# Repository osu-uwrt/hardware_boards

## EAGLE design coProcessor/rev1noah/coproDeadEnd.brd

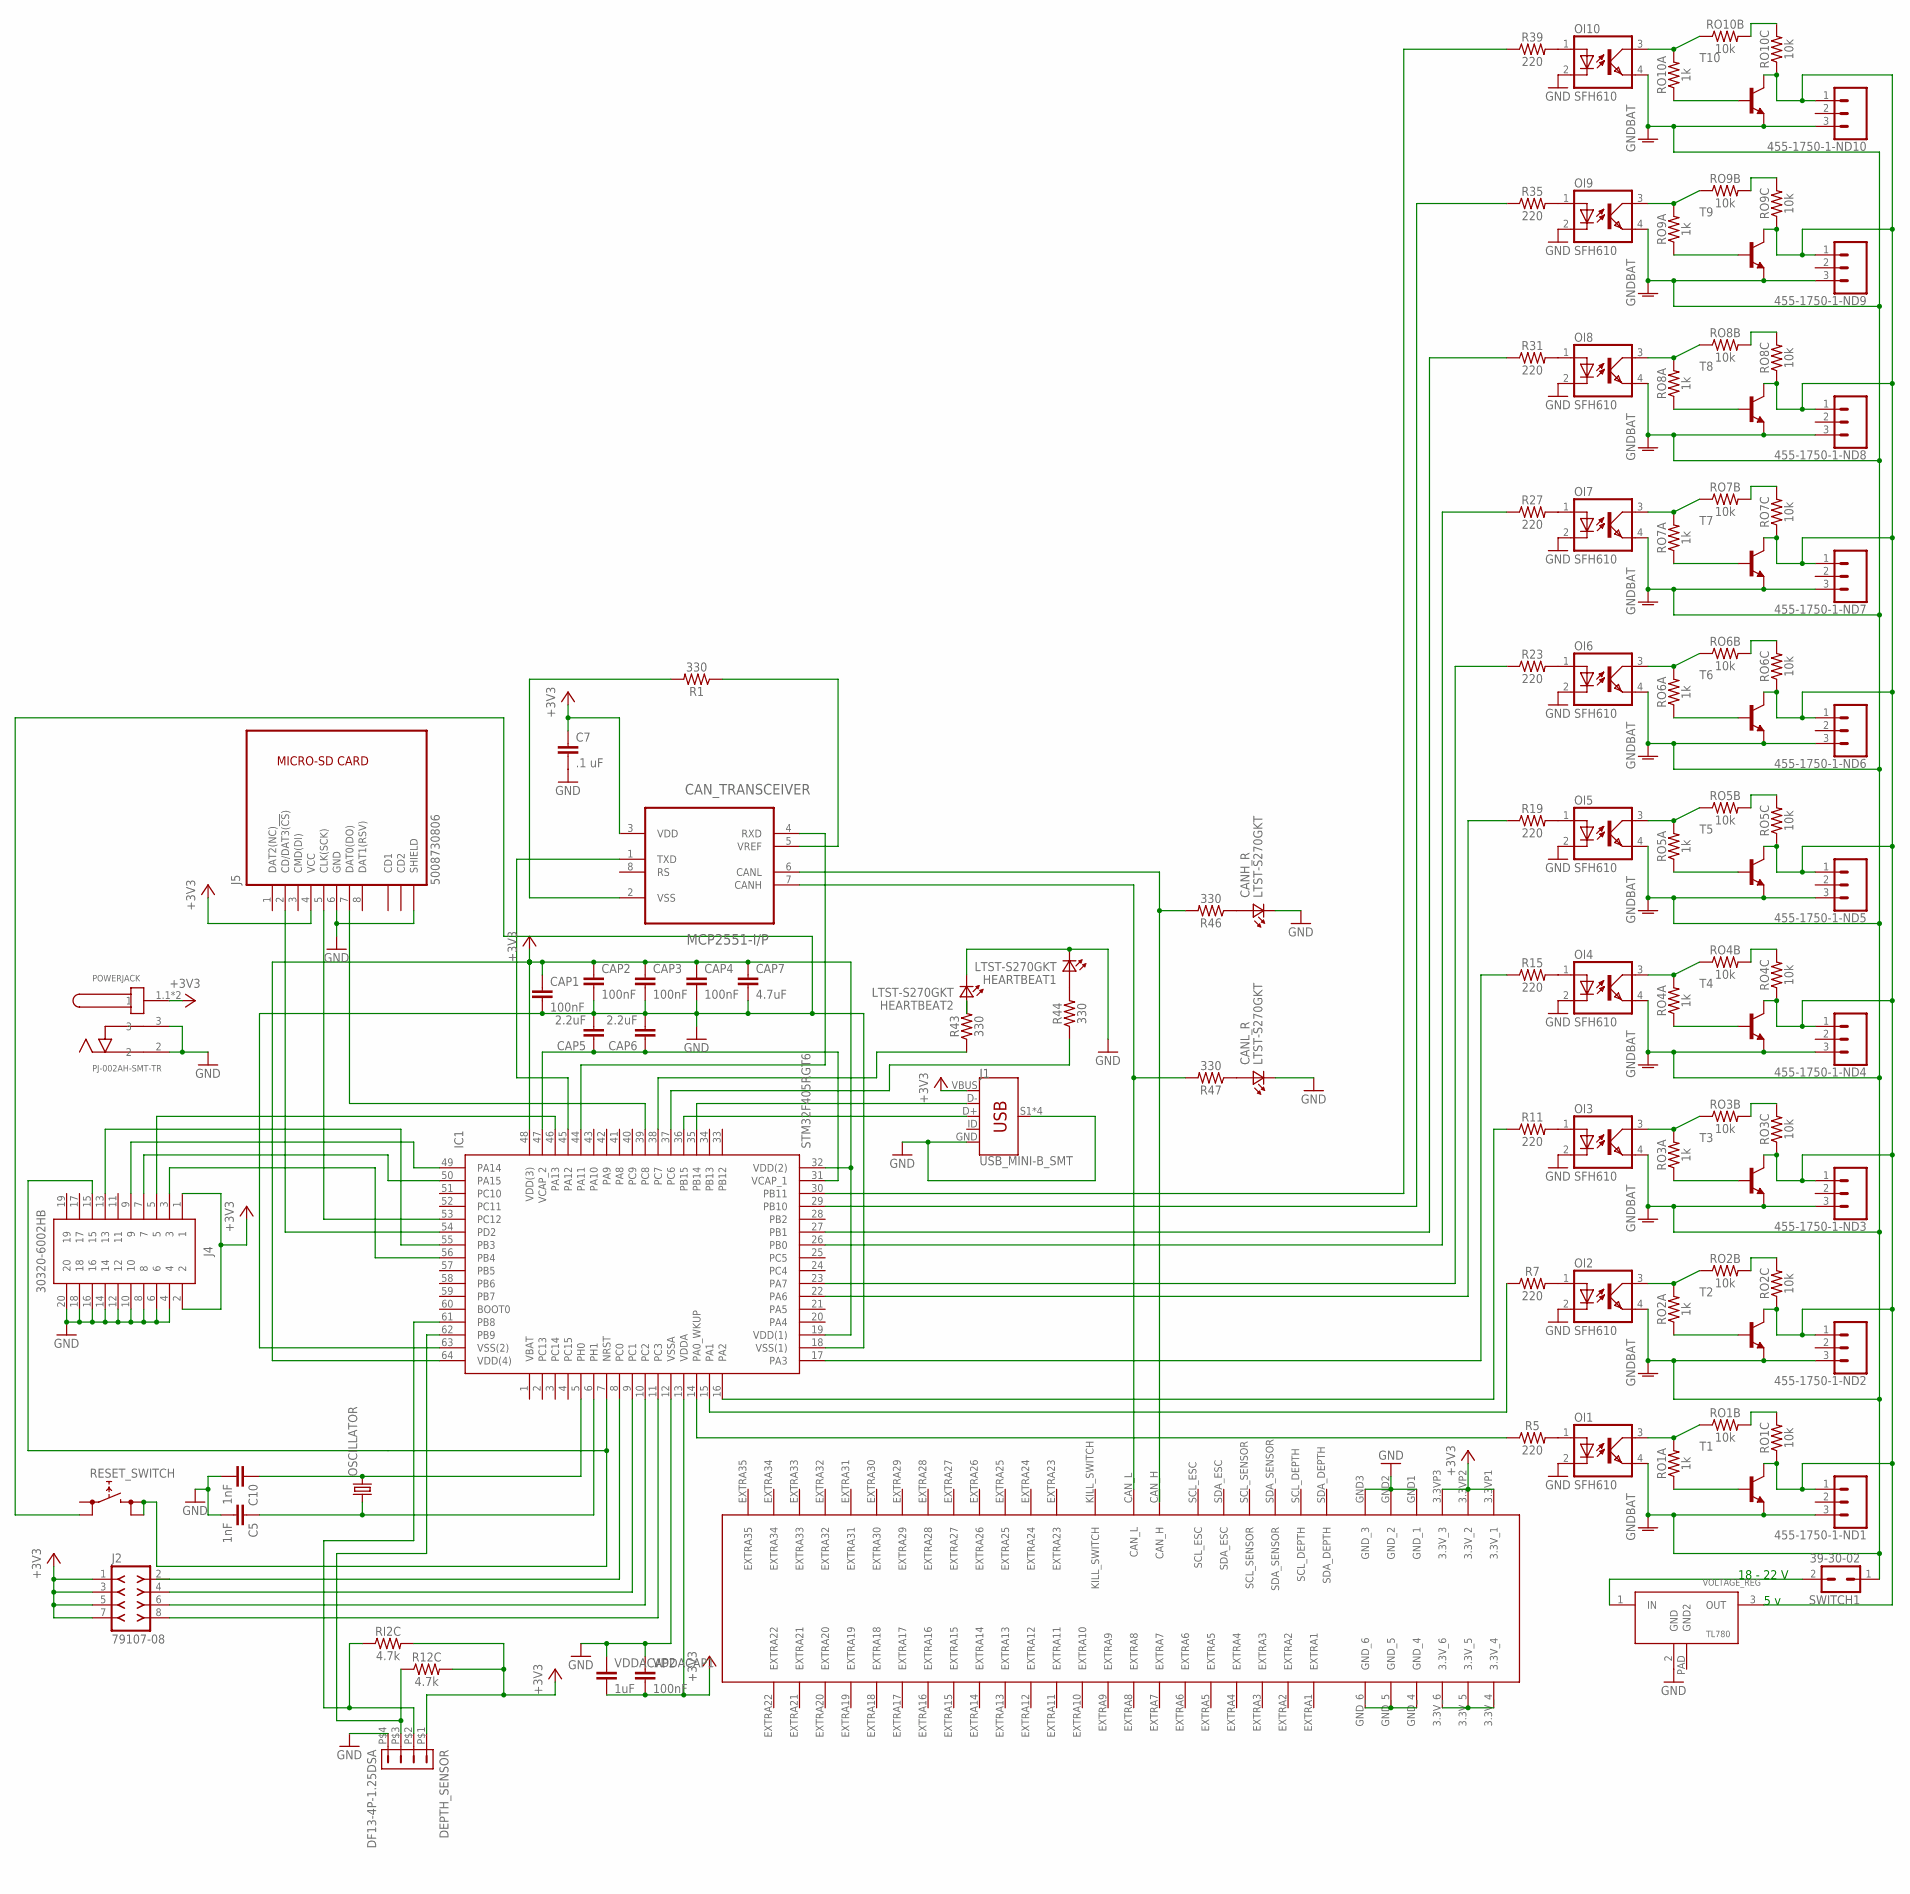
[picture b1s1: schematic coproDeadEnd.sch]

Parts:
455-1750-1-ND1, 455-1750-1-ND2, 455-1750-1-ND3, 455-1750-1-ND4, 455-1750-1-ND5, 455-1750-1-ND6, 455-1750-1-ND7, 455-1750-1-ND8, 455-1750-1-ND9, 455-1750-1-ND10: CONN_03; 1X03
C5, C10: 1nF; 0603
C7: .1 uF; 0603
CANH_R: LTST-S270GKT; 0603
CANL_R: LTST-S270GKT; 0603
CAN_TRANSCEIVER: MCP2551-I/P; DIP254P762X432-8
CAP1, CAP2, CAP3, CAP4: 100nF; 0603
CAP5, CAP6: 2.2uF; 0603
CAP7: 4.7uF; 0603
DEPTH_SENSOR: DF13-4P-1.25DSA
HEARTBEAT1, HEARTBEAT2: LTST-S270GKT; 0603
IC1: STM32F405RGT6; QFP50P1200X1200X160-64N
J1: USB_MINI-B_SMT; USB-MINIB
J2: 79107-08
J4: 30320-6002HB; SHDR20W81P254_2X10_3300X840X93
J5: 5008730806
OI1, OI2, OI3, OI4, OI5, OI6, OI7, OI8, OI9, OI10: SFH610; DIL04
OSCILLATOR: CRYSTALHC49S; HC49/S
POWERJACK: PJ-002AH-SMT-TR; CUI_PJ-002AH-SMT-TR
R1, R43, R44, R46, R47: 330; 0603
R5, R7, R11, R15, R19, R23, R27, R31, R35, R39: 220; 0603
R12C: 4.7k; 0603
RESET_SWITCH: REKN
RI2C: 4.7k; 0603
RO1A, RO2A, RO3A, RO4A, RO5A, RO6A, RO7A, RO8A, RO9A, RO10A: 1k; 0603
RO1B, RO1C, RO2B, RO2C, RO3B, RO3C, RO4B, RO4C, RO5B, RO5C, RO6B, RO6C, RO7B, RO7C, RO8B, RO8C, RO9B, RO9C, RO10B, RO10C: 10k; 0603
SWITCH1: 39-30-02; 39-30-?02?
T1, T2, T3, T4, T5, T6, T7, T8, T9, T10: -NPN-TO126V; TO126V
U$1: 5530843; 5530843-6-BOARDFINGERS
VDDACAP1: 100nF; 0603
VDDACAP2: 1uF; 0603
VOLTAGE_REG: TL780_VREG; D2PAK-3

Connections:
2: IC1.8 (PC0), J2.2
3.3V: C7.1, CAN_TRANSCEIVER.3 (VDD), CAP1.1, CAP2.1, CAP3.1, CAP4.1, CAP7.1, DEPTH_SENSOR.P$1 (1), IC1.13 (VDDA), IC1.19 (VDD(1)), IC1.32 (VDD(2)), IC1.48 (VDD(3)), IC1.64 (VDD(4)), J1.VBUS, J2.1, J2.3, J2.5, J2.7, J4.1, J4.2, J5.4 (VCC), POWERJACK.1.1 (1), POWERJACK.1.2 (1), R12C.2, RI2C.2, U$1.3.3VP1 (3.3V_1), U$1.3.3VP2 (3.3V_2), U$1.3.3VP3 (3.3V_3), VDDACAP1.2, VDDACAP2.2
4: IC1.9 (PC1), J2.4
6: IC1.10 (PC2), J2.6
8: IC1.11 (PC3), J2.8
CANH: CAN_TRANSCEIVER.6 (CANL), R46.2, U$1.CAN_H
CANL: CAN_TRANSCEIVER.7 (CANH), R47.2, U$1.CAN_L
CLK: IC1.53 (PC12), J5.5 (CLK(SCK))
CMD: IC1.54 (PD2), J5.2 (CD/DAT3(!CS!))
D+: IC1.36 (PB15), J1.D+
D-: IC1.35 (PB14), J1.D-
DATO: IC1.39 (PC8), J5.7 (DAT0(DO))
GND: C5.2, C7.2, C10.2, CANH_R.1 (K2), CANL_R.1 (K2), CAP1.2, CAP2.2, CAP3.2, CAP4.2, CAP5.2, CAP6.2, CAP7.2, DEPTH_SENSOR.P$4 (4), HEARTBEAT1.1 (K2), HEARTBEAT2.1 (K2), IC1.12 (VSSA), IC1.18 (VSS(1)), IC1.63 (VSS(2)), J1.GND, J1.S1 (SHIELD), J1.S2 (SHIELD), J1.S3 (SHIELD), J1.S4 (SHIELD), J4.4, J4.6, J4.8, J4.10, J4.12, J4.14, J4.16, J4.18, J4.20, J5.6 (GND), J5.S3 (SHIELD), J5.S4 (SHIELD), OI1.2 (C), OI2.2 (C), OI3.2 (C), OI4.2 (C), OI5.2 (C), OI6.2 (C), OI7.2 (C), OI8.2 (C), OI9.2 (C), OI10.2 (C), POWERJACK.2, POWERJACK.3, RESET_SWITCH.0B (0), U$1.GND1 (GND_1), U$1.GND2 (GND_2), U$1.GND3 (GND_3), U$1.GND_4, U$1.GND_5, U$1.GND_6, VDDACAP1.1, VDDACAP2.1, VOLTAGE_REG.2 (GND)
GNDBAT: 455-1750-1-ND1.3, 455-1750-1-ND2.3, 455-1750-1-ND3.3, 455-1750-1-ND4.3, 455-1750-1-ND5.3, 455-1750-1-ND6.3, 455-1750-1-ND7.3, 455-1750-1-ND8.3, 455-1750-1-ND9.3, 455-1750-1-ND10.3, OI1.4 (EMIT), OI2.4 (EMIT), OI3.4 (EMIT), OI4.4 (EMIT), OI5.4 (EMIT), OI6.4 (EMIT), OI7.4 (EMIT), OI8.4 (EMIT), OI9.4 (EMIT), OI10.4 (EMIT), SWITCH1.1, T1.1 (E), T2.1 (E), T3.1 (E), T4.1 (E), T5.1 (E), T6.1 (E), T7.1 (E), T8.1 (E), T9.1 (E), T10.1 (E)
HEARTBEAT1: IC1.37 (PC6), R44.1
HEARTBEAT2: IC1.38 (PC7), R43.1
JTAG3: IC1.56 (PB4), J4.3
JTAG5: IC1.46 (PA13), J4.5
JTAG9: IC1.49 (PA14), J4.9
JTAG13: IC1.55 (PB3), J4.13
JTAG15: IC1.7 (NRST), J4.15, RESET_SWITCH.1A (1), RESET_SWITCH.1B (1)
unnamed: OI2.3 (COL), RO2A.2, RO2B.1
unnamed: RO1A.1, T1.3 (B)
unnamed: OI1.1 (A), R5.2
unnamed: CAN_TRANSCEIVER.2 (VSS), R1.2
unnamed: OI1.3 (COL), RO1A.2, RO1B.1
unnamed: SWITCH1.2, VOLTAGE_REG.1 (IN)
unnamed: CANL_R.2 (A2), R47.1
unnamed: RO2A.1, T2.3 (B)
unnamed: RO1B.2, RO1C.2
unnamed: OI2.1 (A), R7.2
unnamed: CAN_TRANSCEIVER.5 (VREF), R1.1
unnamed: IC1.14 (PA0_WKUP), R5.1
unnamed: HEARTBEAT2.2 (A2), R43.2
unnamed: RO2B.2, RO2C.2
unnamed: OI3.3 (COL), RO3A.2, RO3B.1
unnamed: RO3A.1, T3.3 (B)
unnamed: 455-1750-1-ND1.1, 455-1750-1-ND2.1, 455-1750-1-ND3.1, 455-1750-1-ND4.1, 455-1750-1-ND5.1, 455-1750-1-ND6.1, 455-1750-1-ND7.1, 455-1750-1-ND8.1, 455-1750-1-ND9.1, 455-1750-1-ND10.1, RO1C.1, RO2C.1, RO3C.1, RO4C.1, RO5C.1, RO6C.1, RO7C.1, RO8C.1, RO9C.1, RO10C.1, T1.2 (C), T2.2 (C), T3.2 (C), T4.2 (C), T5.2 (C), T6.2 (C), T7.2 (C), T8.2 (C), T9.2 (C), T10.2 (C), VOLTAGE_REG.3 (OUT)
unnamed: OI3.1 (A), R11.2
unnamed: RO3B.2, RO3C.2
unnamed: OI4.3 (COL), RO4A.2, RO4B.1
unnamed: RO4A.1, T4.3 (B)
unnamed: OI4.1 (A), R15.2
unnamed: HEARTBEAT1.2 (A2), R44.2
unnamed: RO4B.2, RO4C.2
unnamed: OI5.3 (COL), RO5A.2, RO5B.1
unnamed: RO5A.1, T5.3 (B)
unnamed: OI5.1 (A), R19.2
unnamed: CANH_R.2 (A2), R46.1
unnamed: RO5B.2, RO5C.2
unnamed: OI6.3 (COL), RO6A.2, RO6B.1
unnamed: RO6A.1, T6.3 (B)
unnamed: OI6.1 (A), R23.2
unnamed: RO6B.2, RO6C.2
unnamed: OI7.3 (COL), RO7A.2, RO7B.1
unnamed: RO7A.1, T7.3 (B)
unnamed: OI7.1 (A), R27.2
unnamed: RO7B.2, RO7C.2
unnamed: OI8.3 (COL), RO8A.2, RO8B.1
unnamed: RO8A.1, T8.3 (B)
unnamed: OI8.1 (A), R31.2
unnamed: RO8B.2, RO8C.2
unnamed: OI9.3 (COL), RO9A.2, RO9B.1
unnamed: RO9A.1, T9.3 (B)
unnamed: OI9.1 (A), R35.2
unnamed: RO9B.2, RO9C.2
unnamed: OI10.3 (COL), RO10A.2, RO10B.1
unnamed: RO10A.1, T10.3 (B)
unnamed: OI10.1 (A), R39.2
unnamed: RO10B.2, RO10C.2
OI2: IC1.15 (PA1), R7.1
OI3: IC1.16 (PA2), R11.1
OI4: IC1.17 (PA3), R15.1
OI5: IC1.22 (PA6), R19.1
OI6: IC1.23 (PA7), R23.1
OI7: IC1.26 (PB0), R27.1
OI8: IC1.27 (PB1), R31.1
OI10: IC1.30 (PB11), R39.1
OIO9: IC1.29 (PB10), R35.1
OSC1: C5.1, IC1.6 (PH1), OSCILLATOR.1
OSC2: C10.1, IC1.5 (PH0), OSCILLATOR.2
P$2: DEPTH_SENSOR.P$2 (2), IC1.61 (PB8), RI2C.1
PA15: IC1.50 (PA15), J4.7
POWER: U$1.3.3V_4, U$1.3.3V_5, U$1.3.3V_6
PS$3: DEPTH_SENSOR.P$3 (3), IC1.62 (PB9), R12C.1
RXD: CAN_TRANSCEIVER.4 (RXD), IC1.44 (PA11)
TXD: CAN_TRANSCEIVER.1 (TXD), IC1.45 (PA12)
VCAP_2TO1: CAP5.1, CAP6.1, IC1.31 (VCAP_1), IC1.47 (VCAP_2)

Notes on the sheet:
5 v
18 - 22 V

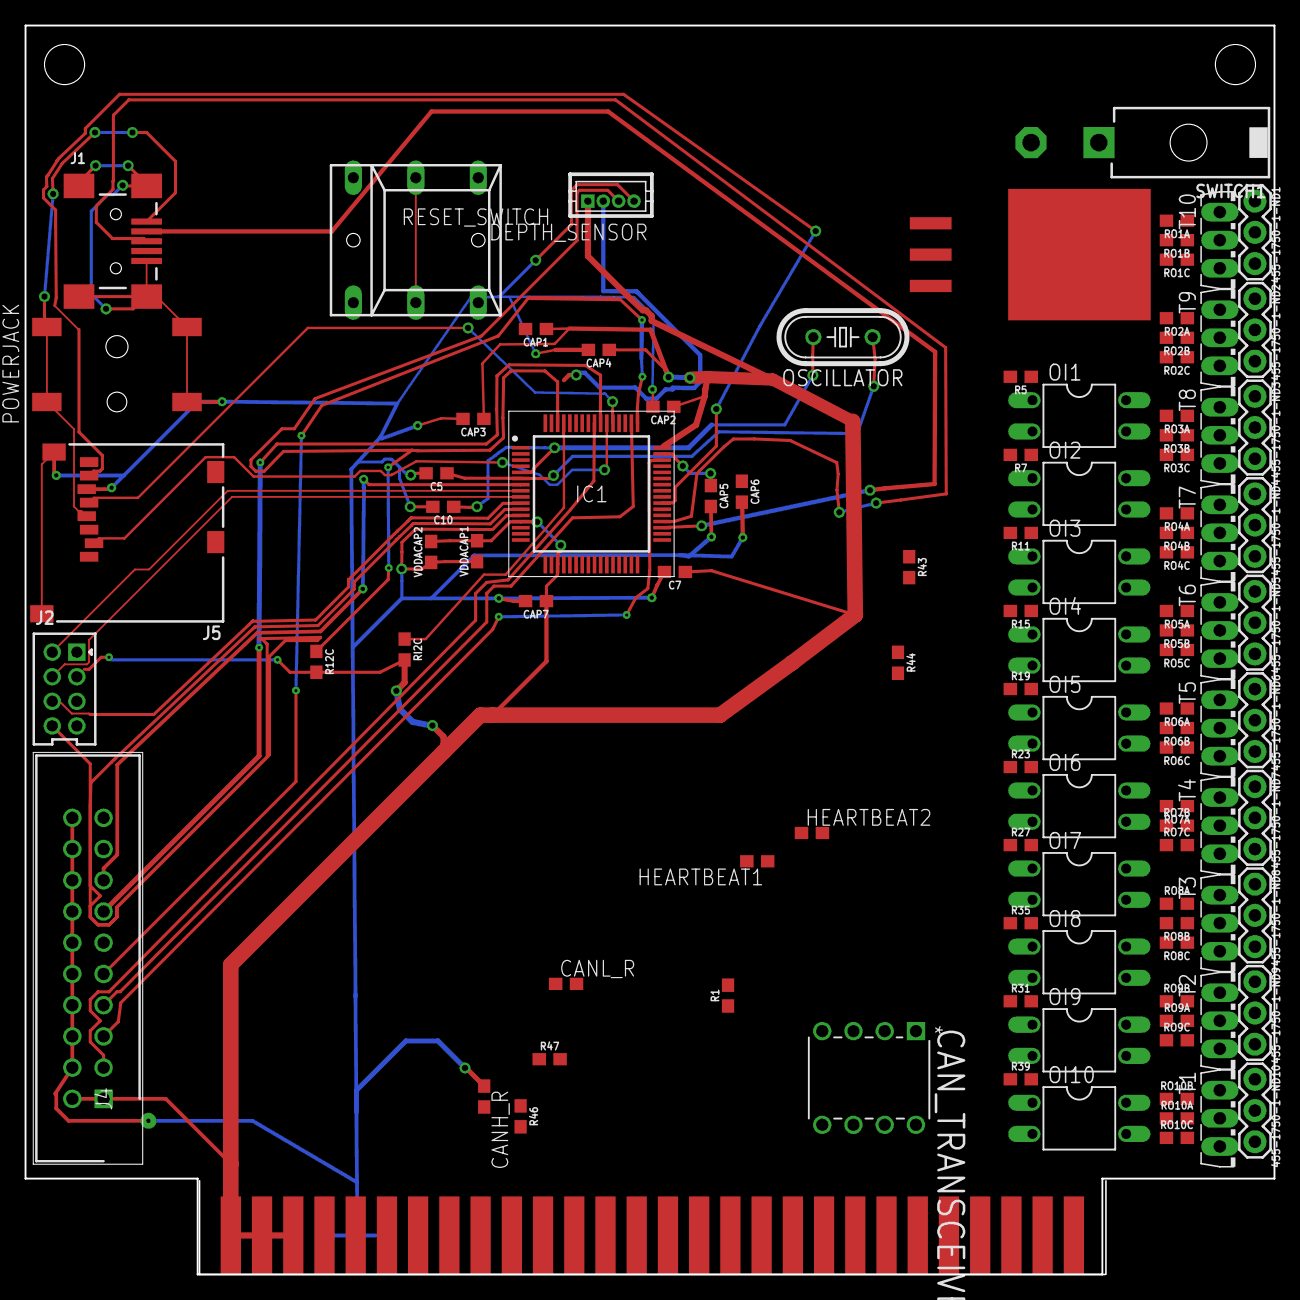
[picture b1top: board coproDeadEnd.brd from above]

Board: 2 copper layers, 101.6 x 101.6 mm, 106 parts (0 on the bottom side), 88 nets.

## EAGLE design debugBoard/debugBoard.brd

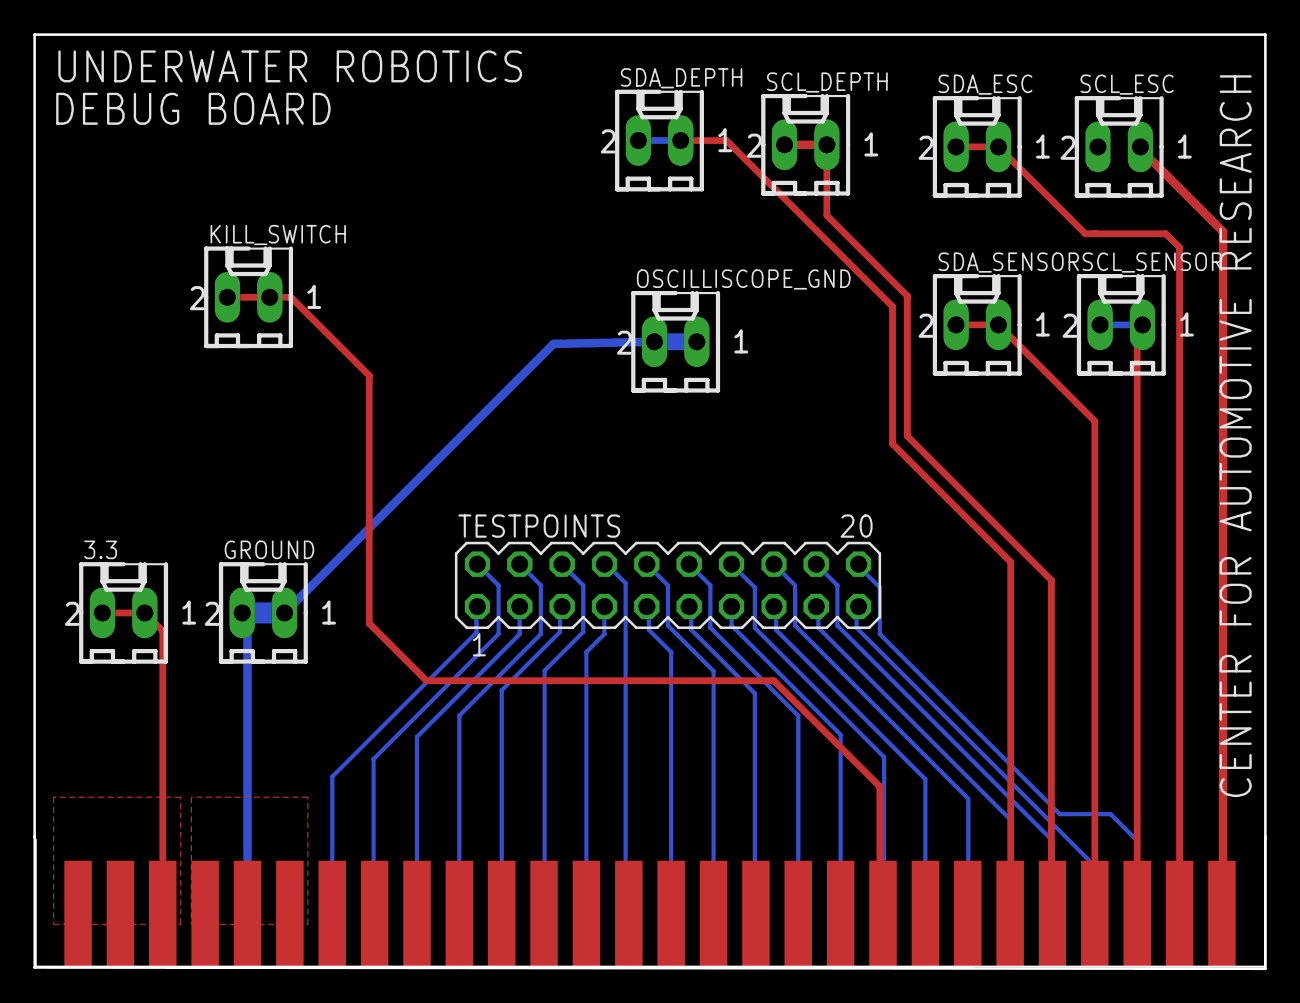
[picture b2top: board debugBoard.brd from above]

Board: 2 copper layers, 73.8 x 56.0 mm, 12 parts (0 on the bottom side), 29 nets.

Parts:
3.3: 22-27-2021-02; 6410-02
GROUND: 22-27-2021-02; 6410-02
KILL_SWITCH: 22-27-2021-02; 6410-02
OSCILLISCOPE_GND: 22-27-2021-02; 6410-02
SCL_DEPTH: 22-27-2021-02; 6410-02
SCL_ESC: 22-27-2021-02; 6410-02
SCL_SENSOR: 22-27-2021-02; 6410-02
SDA_DEPTH: 22-27-2021-02; 6410-02
SDA_ESC: 22-27-2021-02; 6410-02
SDA_SENSOR: 22-27-2021-02; 6410-02
TESTPOINTS: MA10-2
U$1: 5530843; 5530843-6-BOARDFINGERS

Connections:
3.3V: 3.3.1, 3.3.2, U$1.3.3VP1, U$1.3.3VP2, U$1.3.3VP3, U$1.3.3V_4, U$1.3.3V_5, U$1.3.3V_6
EXTRA1: TESTPOINTS.1, U$1.EXTRA1
EXTRA2: TESTPOINTS.2, U$1.EXTRA2
EXTRA3: TESTPOINTS.3, U$1.EXTRA3
EXTRA4: TESTPOINTS.4, U$1.EXTRA4
EXTRA5: TESTPOINTS.5, U$1.EXTRA5
EXTRA6: TESTPOINTS.6, U$1.EXTRA6
EXTRA7: TESTPOINTS.7, U$1.EXTRA7
EXTRA8: TESTPOINTS.8, U$1.EXTRA8
EXTRA9: TESTPOINTS.9, U$1.EXTRA9
EXTRA10: TESTPOINTS.10, U$1.EXTRA10
EXTRA11: TESTPOINTS.11, U$1.EXTRA11
EXTRA12: TESTPOINTS.12, U$1.EXTRA12
EXTRA13: TESTPOINTS.13, U$1.EXTRA13
EXTRA14: TESTPOINTS.14, U$1.EXTRA14
EXTRA15: TESTPOINTS.15, U$1.EXTRA15
EXTRA16: TESTPOINTS.16, U$1.EXTRA16
EXTRA17: TESTPOINTS.17, U$1.EXTRA17
EXTRA18: TESTPOINTS.18, U$1.EXTRA18
EXTRA19: TESTPOINTS.19, U$1.EXTRA19
EXTRA20: TESTPOINTS.20, U$1.EXTRA20
GND: GROUND.1, GROUND.2, OSCILLISCOPE_GND.1, OSCILLISCOPE_GND.2, U$1.GND1, U$1.GND2, U$1.GND3, U$1.GND_4, U$1.GND_5, U$1.GND_6
KILL_SWITCH: KILL_SWITCH.1, KILL_SWITCH.2, U$1.KILL_SWITCH
SCL_DEPTH: SCL_DEPTH.1, SCL_DEPTH.2, U$1.SCL_DEPTH
SCL_ESC: SCL_ESC.1, SCL_ESC.2, U$1.SCL_ESC
SCL_SENSOR: SCL_SENSOR.1, SCL_SENSOR.2, U$1.SCL_SENSOR
SDA_DEPTH: SDA_DEPTH.1, SDA_DEPTH.2, U$1.SDA_DEPTH
SDA_ESC: SDA_ESC.1, SDA_ESC.2, U$1.SDA_ESC
SDA_SENSOR: SDA_SENSOR.1, SDA_SENSOR.2, U$1.SDA_SENSOR

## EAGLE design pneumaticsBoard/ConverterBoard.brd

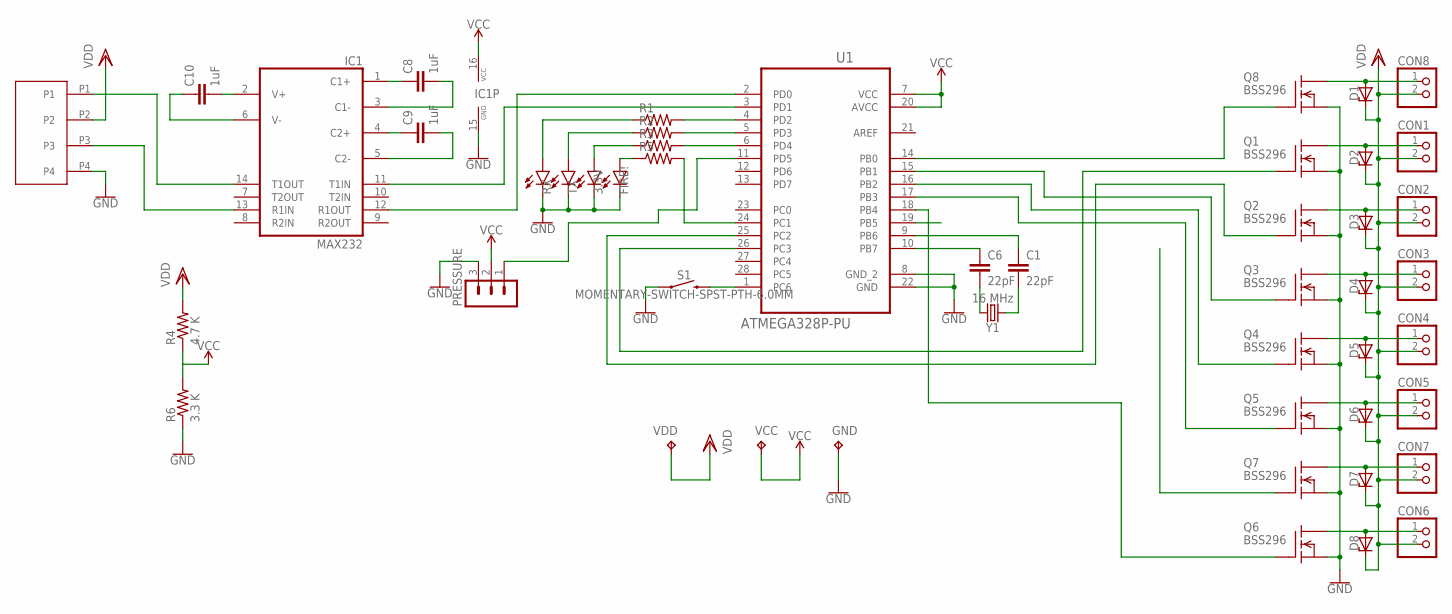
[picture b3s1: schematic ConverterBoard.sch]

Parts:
3.3V: BLUE; LED-0603
C1, C6: 22pF; 0603
C8, C9, C10: 1uF; 0603
CON1, CON2, CON3, CON4, CON5, CON6, CON7, CON8: PINHD-1X2; 1X02
D1, D2, D3, D4, D5, D6, D7, D8: BZX90; DO34Z7
FIRE!: BLUE; LED-0603
GND: TPTP11R; TP11R
IC1: MAX232; DIL16
PRESSURE: MA03-1
Q1, Q2, Q3, Q4, Q5, Q6, Q7, Q8: BSS296; TO92
R1, R2, R3, R5: R-US_0204/2V; 0204V
R4: 4.7 K; 0204V
R6: 3.3 K; 0204V
RX: BLUE; LED-0603
S1: MOMENTARY-SWITCH-SPST-PTH-6.0MM; TACTILE_SWITCH_PTH_6.0MM
TX: BLUE; LED-0603
U1: ATMEGA328P-PU; DIP254P762X457-28
U$2: MINI_FIT_JR_4PIN_VERT
VCC: TPTP11R; TP11R
VDD: TPTP11R; TP11R
Y1: 16 MHz; HC49U

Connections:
CON1_GND: CON1.1, D2.A, Q1.2 (D)
CON2_GND: CON2.1, D3.A, Q2.2 (D)
CON3_GND: CON3.1, D4.A, Q3.2 (D)
CON4_GND: CON4.1, D5.A, Q4.2 (D)
CON5_GND: CON5.1, D6.A, Q5.2 (D)
CON6_GND: CON6.1, D8.A, Q6.2 (D)
CON7_GND: CON7.1, D7.A, Q7.2 (D)
CON8_GND: CON8.1, D1.A, Q8.2 (D)
GND: 3.3V.C, FIRE!.C, GND.TP, IC1.15 (GND), PRESSURE.3, Q1.3 (S), Q2.3 (S), Q3.3 (S), Q4.3 (S), Q5.3 (S), Q6.3 (S), Q7.3 (S), Q8.3 (S), R6.1, RX.C, S1.1, TX.C, U1.8 (GND_2), U1.22 (GND), U$2.P4
unnamed: R3.2, U1.6 (PD4)
unnamed: FIRE!.A, R5.1
unnamed: R4.1, R6.2
unnamed: R5.2, U1.24 (PC1)
unnamed: C6.2, Y1.2
unnamed: PRESSURE.1, U1.11 (PD5)
unnamed: R1.2, U1.4 (PD2)
unnamed: R2.2, U1.5 (PD3)
unnamed: C8.1, IC1.1 (C1+)
unnamed: C9.1, IC1.4 (C2+)
unnamed: C8.2, IC1.3 (C1-)
unnamed: C9.2, IC1.5 (C2-)
unnamed: C10.2, IC1.2 (V+)
unnamed: C10.1, IC1.6 (V-)
unnamed: C1.2, Y1.1
POWER: 3.3V.A, R3.1
Q1: Q1.1 (G), U1.26 (PC3)
Q2: Q2.1 (G), U1.25 (PC2)
Q3: Q3.1 (G), U1.15 (PB1)
Q4: Q4.1 (G), U1.16 (PB2)
Q5: Q5.1 (G), U1.17 (PB3)
Q6: Q6.1 (G), U1.18 (PB4)
Q7: Q7.1 (G), U1.19 (PB5)
Q8: Q8.1 (G), U1.14 (PB0)
RESET: S1.3 (2), U1.1 (PC6)
RS232_RX-ATMEGA_TX: IC1.12 (R1OUT), U1.2 (PD0)
RS232_TX-ATMEGA_RX: IC1.11 (T1IN), U1.3 (PD1)
RX: IC1.13 (R1IN), U$2.P3
RX_ON: R1.1, RX.A
TX: IC1.14 (T1OUT), U$2.P1
TX_ON: R2.1, TX.A
VCC: IC1.16 (VCC), PRESSURE.2, U1.7 (VCC), U1.20 (AVCC), VCC.TP
VDD: CON1.2, CON2.2, CON3.2, CON4.2, CON5.2, CON6.2, CON7.2, CON8.2, D1.C, D2.C, D3.C, D4.C, D5.C, D6.C, D7.C, D8.C, R4.2, U$2.P2, VDD.TP
XTAL1: C1.1, U1.9 (PB6)
XTAL2: C6.1, U1.10 (PB7)

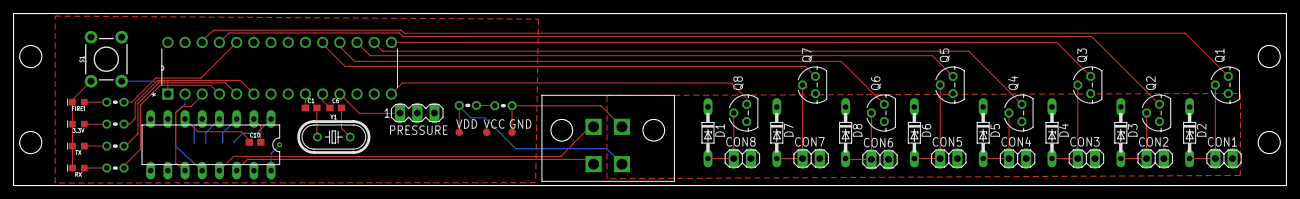
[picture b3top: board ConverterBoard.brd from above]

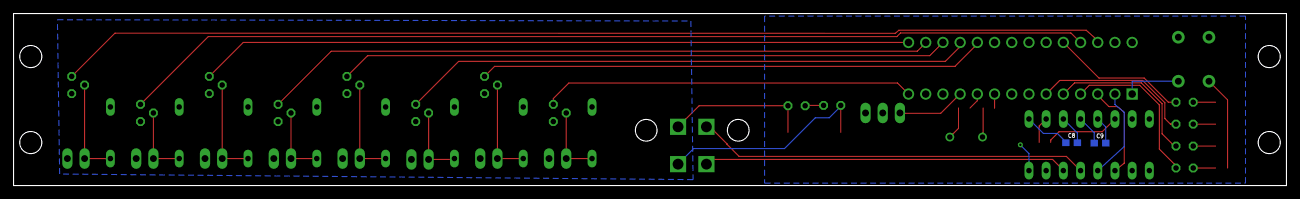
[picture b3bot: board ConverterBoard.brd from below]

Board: 2 copper layers, 188.0 x 25.4 mm, 48 parts (2 on the bottom side), 44 nets.

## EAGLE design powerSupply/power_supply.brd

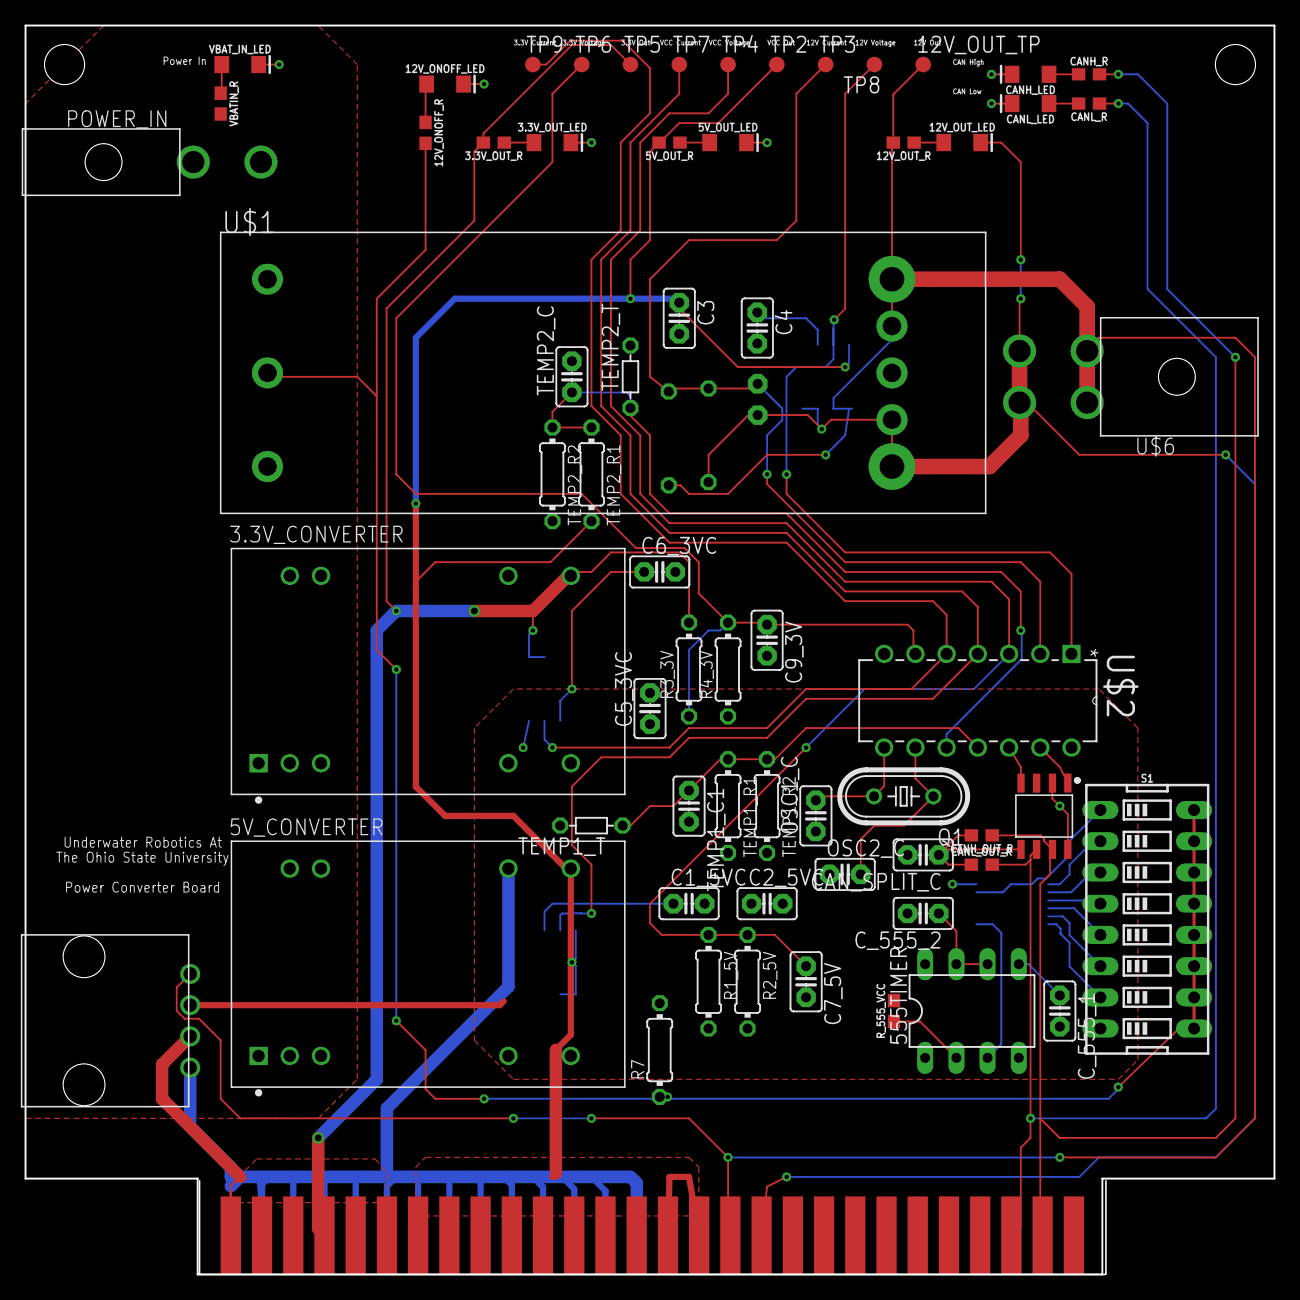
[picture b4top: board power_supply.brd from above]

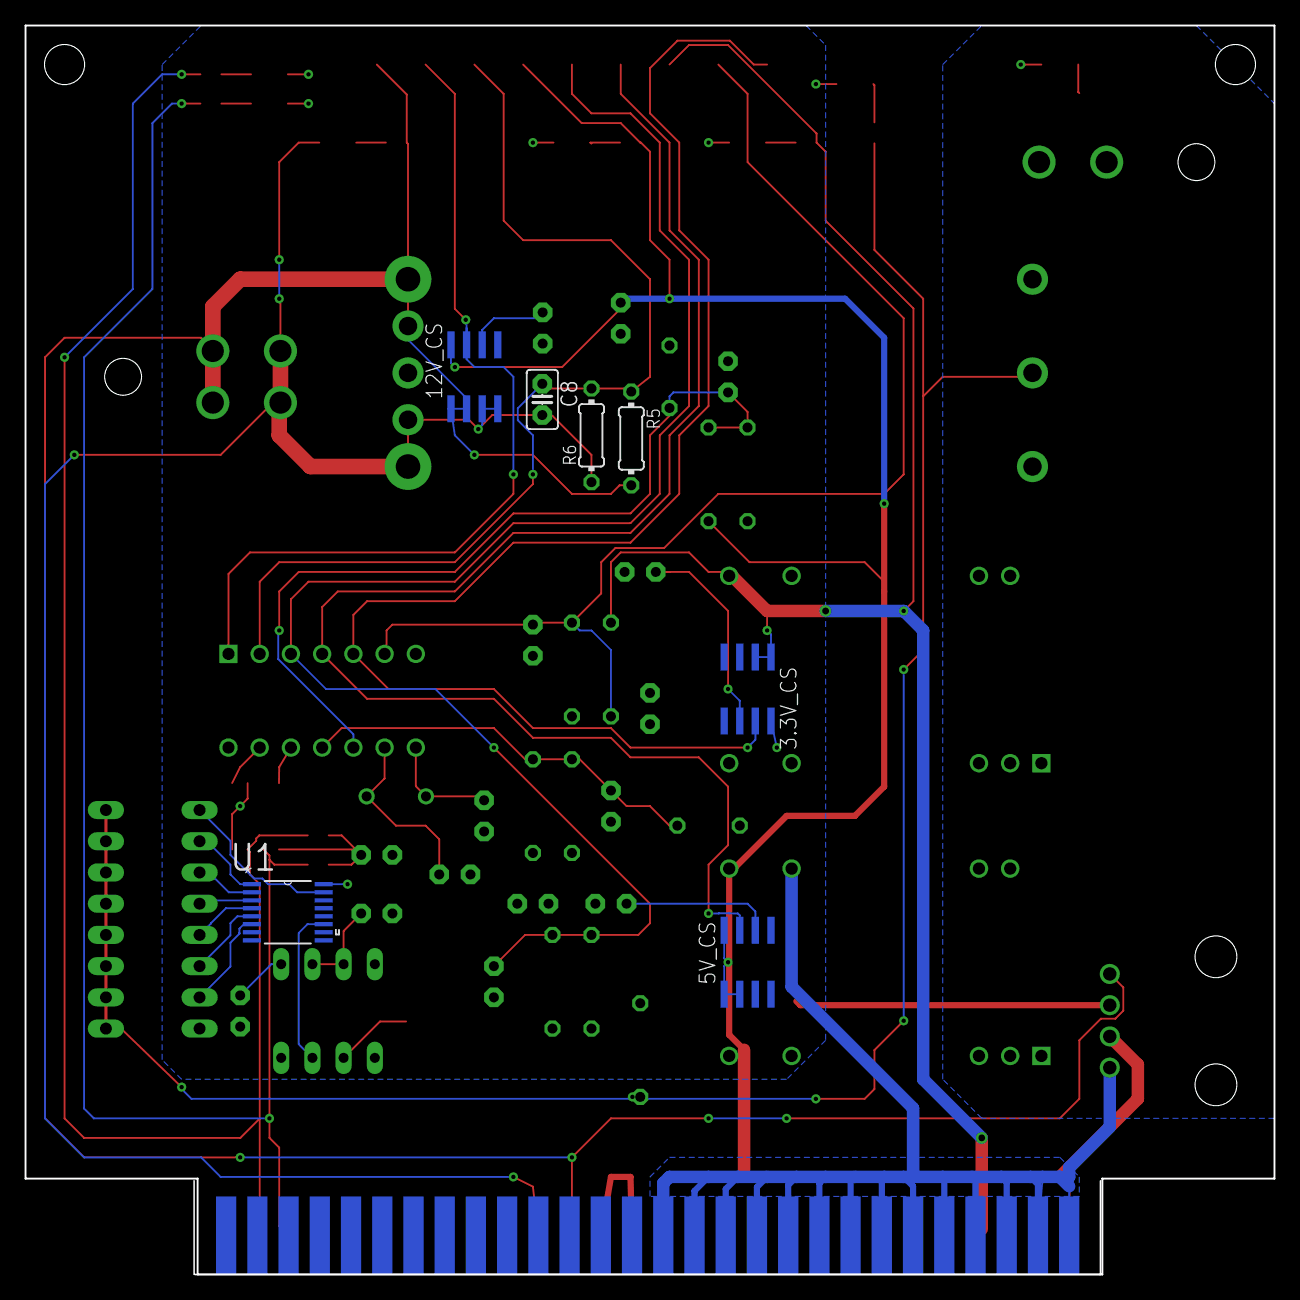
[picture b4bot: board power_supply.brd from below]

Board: 2 copper layers, 101.6 x 101.6 mm, 71 parts (7 on the bottom side), 44 nets.

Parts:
3.3V_CONVERTER: NCS12S1203C; CONV_NCS12S1203C
3.3V_CS, 5V_CS, 12V_CS: ACS712-LC; SOIC8
3.3V_OUT_LED, 5V_OUT_LED, 12V_ONOFF_LED, 12V_OUT_LED: LED-1206
3.3V_OUT_R, 5V_OUT_R, 12V_ONOFF_R, 12V_OUT_R: 330; 0603
5V_CONVERTER: NCS12S1205C; CONV_NCS12S1205C
12V_OUT_TP: PTR1B1,27; B1,27
555TIMER: NE555; DIL-08
C1_5VC, C4, C6_3VC: 1 nF; C2.5-2
C2_5VC, C3, C5_3VC, C7_5V, C8, C9_3V: 0.1 uF; C2.5-2
CANH_LED: LED-1206
CANH_OUT_R: 60; 0603
CANH_R: 330; 0603
CANL_LED: LED-1206
CANL_OUT_R: 60; 0603
CANL_R: 330; 0603
CAN_SPLIT_C: 4700pF; C2.5-2
C_555_1: 10nF; C2.5-2
C_555_2: 100 uF; C2.5-2
MCP2561: MCP2561; SOIC8
OSC1_C: 1nF; C2.5-2
OSC2_C: 1 nF; C2.5-2
POWER_IN: 39-30-1020; 5569-02A2
Q1: HC49/S
R1_5V, R2_5V, R3_3V, R4_3V, R5, R6, R7: 0204/7
R_555_VCC: 10000; 0603
S1: DIPSWITCH-08
TEMP1_C1, TEMP2_C: 0.1 uF; C2.5-2
TEMP1_R1, TEMP1_R2, TEMP2_R1, TEMP2_R2: 0204/7
TEMP1_T, TEMP2_T: THERMISTOR-5; R-5
TP2, TP3, TP4, TP5, TP6, TP7, TP8, TP9: PTR1B1,27; B1,27
U1: SN74HC595PW; SOP65P640X120-16N
U$1: UIE48T10120
U$2: MCP25020-I/P; DIP254P762X432-14
U$4: 5530843-6-STS; 5530843-6-BOARD
U$6: 39-30-1040; 5569-04A2
U$7: 70555-0003
VBATIN_R: 330; 0603
VBAT_IN_LED: LED-1206

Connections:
3.3V_ANA_CUR_OUT: 3.3V_CS.7, TP9.TP, U$2.5
3.3V_OUT: 3.3V_CONVERTER.14, 3.3V_CS.1, 3.3V_CS.2, 3.3V_OUT_R.2, R3_3V.2, TP5.TP, U$4.1, U$4.3, U$4.5, U$4.7, U$4.9, U$4.11, U$7.2
3.3V_OUT_LED: 3.3V_OUT_LED.A, 3.3V_OUT_R.1
3V_VOL_ANA_OUT: C9_3V.1, R3_3V.1, R4_3V.2, TP6.TP, U$2.6
5V_CUR_ANA_OUT: 5V_CS.7, TP7.TP, U$2.4
5V_OUT_LED: 5V_OUT_LED.A, 5V_OUT_R.1
5V_VOL_ANA_OUT: C7_5V.1, R1_5V.1, R2_5V.1, TP4.TP, U$2.3
12V_CON_ONOFF: 12V_ONOFF_R.2, R7.1, S1.9, S1.10, S1.11, S1.12, S1.13, S1.14, S1.15, S1.16, U$1.ON/OFF
12V_CUR_ANA_OUT: 12V_CS.7, TP8.TP, U$2.1
12V_FILTER: 12V_CS.6, C4.1
12V_GND: 12V_CS.3, 12V_CS.4, 12V_OUT_LED.C, C8.2, R6.1, U$1.VOUT(-), U$1.VOUT_SENSE(-), U$4.35, U$6.3, U$6.4
12V_ONOFF_LED: 12V_ONOFF_LED.A, 12V_ONOFF_R.1
12V_OUT: 12V_CS.1, 12V_CS.2, 12V_OUT_R.2, 12V_OUT_TP.TP, R5.2, U$1.VOUT(+), U$1.VOUT_SENSE(+), U$4.33, U$6.1, U$6.2, U$7.4
12V_OUT_LED: 12V_OUT_LED.A, 12V_OUT_R.1
12V_VOL_ANA_OUT: C8.1, R5.1, R6.2, TP3.TP, U$2.2
555_CON: 555TIMER.5, C_555_1.1
555_TREDIS: 555TIMER.6, 555TIMER.7, C_555_2.1
555_TRIG: 555TIMER.2, R_555_VCC.1
CANH_LED: CANH_LED.A, CANH_R.1
CANH_OUT: CANH_OUT_R.1, CANH_R.2, MCP2561.P$7, U$4.53
CANL_LED: CANL_LED.A, CANL_R.2
CANL_OUT: CANL_OUT_R.2, CANL_R.1, MCP2561.P$6, U$4.51
CAN_SPLIT: CANH_OUT_R.2, CANL_OUT_R.1, CAN_SPLIT_C.1, MCP2561.P$5
FILTER_3V: 3.3V_CS.6, C6_3VC.1
FILTER_5V: 5V_CS.6, C1_5VC.1
GND: 3.3V_CONVERTER.16, 3.3V_CS.3, 3.3V_CS.4, 3.3V_CS.5, 3.3V_OUT_LED.C, 5V_CONVERTER.16, 5V_CS.3, 5V_CS.4, 5V_CS.5, 5V_OUT_LED.C, 12V_CS.5, 12V_ONOFF_LED.C, 555TIMER.1, C1_5VC.2, C2_5VC.2, C3.2, C4.2, C5_3VC.2, C6_3VC.2, C7_5V.2, C9_3V.2, CANH_LED.C, CANL_LED.C, CAN_SPLIT_C.2, C_555_1.2, C_555_2.2, MCP2561.P$2, MCP2561.P$8, OSC1_C.1, OSC2_C.1, R2_5V.2, R4_3V.1, S1.8, TEMP1_C1.2, TEMP1_R2.2, TEMP1_T.2, TEMP2_C.2, TEMP2_R2.2, TEMP2_T.2, U1.8, U$2.7, U$4.2, U$4.4, U$4.6, U$4.8, U$4.10, U$4.12, U$4.14, U$4.16, U$4.18, U$4.20, U$4.22, U$4.24, U$4.26, U$4.28, U$7.1
unnamed: MCP2561.P$4, U$2.12
unnamed: MCP2561.P$1, U$2.13
NAND1: S1.1, U1.15
NAND2: S1.2, U1.1
NAND3: S1.3, U1.2
NAND4: S1.4, U1.3
NAND5: S1.5, U1.4
NAND6: S1.6, U1.5
NAND7: S1.7, U1.6
OSC1: OSC1_C.2, Q1.2, U$2.8
OSC2: OSC2_C.2, Q1.1, U$2.9
OUT555: 555TIMER.3, U1.11
TEMP1_ANA_OUT: TEMP1_C1.1, TEMP1_R1.1, TEMP1_R2.1, TEMP1_T.1, U$2.11
TEMP2_ANA_OUT: TEMP2_C.1, TEMP2_R1.1, TEMP2_R2.1, TEMP2_T.1, U$2.10
VBAT_IN_LED: VBATIN_R.1, VBAT_IN_LED.A
VCC: 3.3V_CS.8, 5V_CONVERTER.14, 5V_CS.1, 5V_CS.2, 5V_CS.8, 5V_OUT_R.2, 12V_CS.8, 555TIMER.4, 555TIMER.8, C2_5VC.1, C3.1, C5_3VC.1, MCP2561.P$3, R1_5V.2, R7.2, R_555_VCC.2, TEMP1_R1.2, TEMP2_R1.2, TP2.TP, U1.16, U$2.14, U$4.13, U$4.15, U$4.17, U$4.19, U$4.21, U$4.23, U$4.25, U$4.27, U$4.29, U$4.31, U$7.3
V_BAT_BAL+: 3.3V_CONVERTER.22, 3.3V_CONVERTER.23, 5V_CONVERTER.22, 5V_CONVERTER.23, POWER_IN.2, U$1.VIN(+), VBATIN_R.2
V_BAT_BAL-: 3.3V_CONVERTER.2, 3.3V_CONVERTER.3, 5V_CONVERTER.2, 5V_CONVERTER.3, POWER_IN.1, U$1.VIN(-), VBAT_IN_LED.C

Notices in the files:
parts and their libraries:
SparkFun-Connectors: Licensing: Creative Commons ShareAlike 4.0 International - https://creativecommons.org/licenses/by-sa/4.0
con-molex-mini-fit: Copyright (C) 2011, Bob Starr
con-molex-milli-grid: Copyright (C) 2010, Bob Starr
